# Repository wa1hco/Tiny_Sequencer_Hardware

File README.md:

# Tiny_Sequencer_Hardware
Schematic, Layout, and component files  
KiCad V8 used for schematic and layout  
ATTiny814 microcontroller  
FTDI230 Serial interface  
Surface mount components  
Back side is grouind plane, a few jumpers, and no components  
Connections via 12 pin screw terminal header with 0.1 inch spacing  
- 4 contact closure outputs using AC/DC optoisolators  
- Key input with return
- 6 to 30V DC input and return

Powered by DC or USB  
Programming via UPDI over USB  
Software able to use serial port for communication  
Status LEDs
- 4 sequencer ouptuts,
- 5V,
- Tx serial activity
- Rx serial activity

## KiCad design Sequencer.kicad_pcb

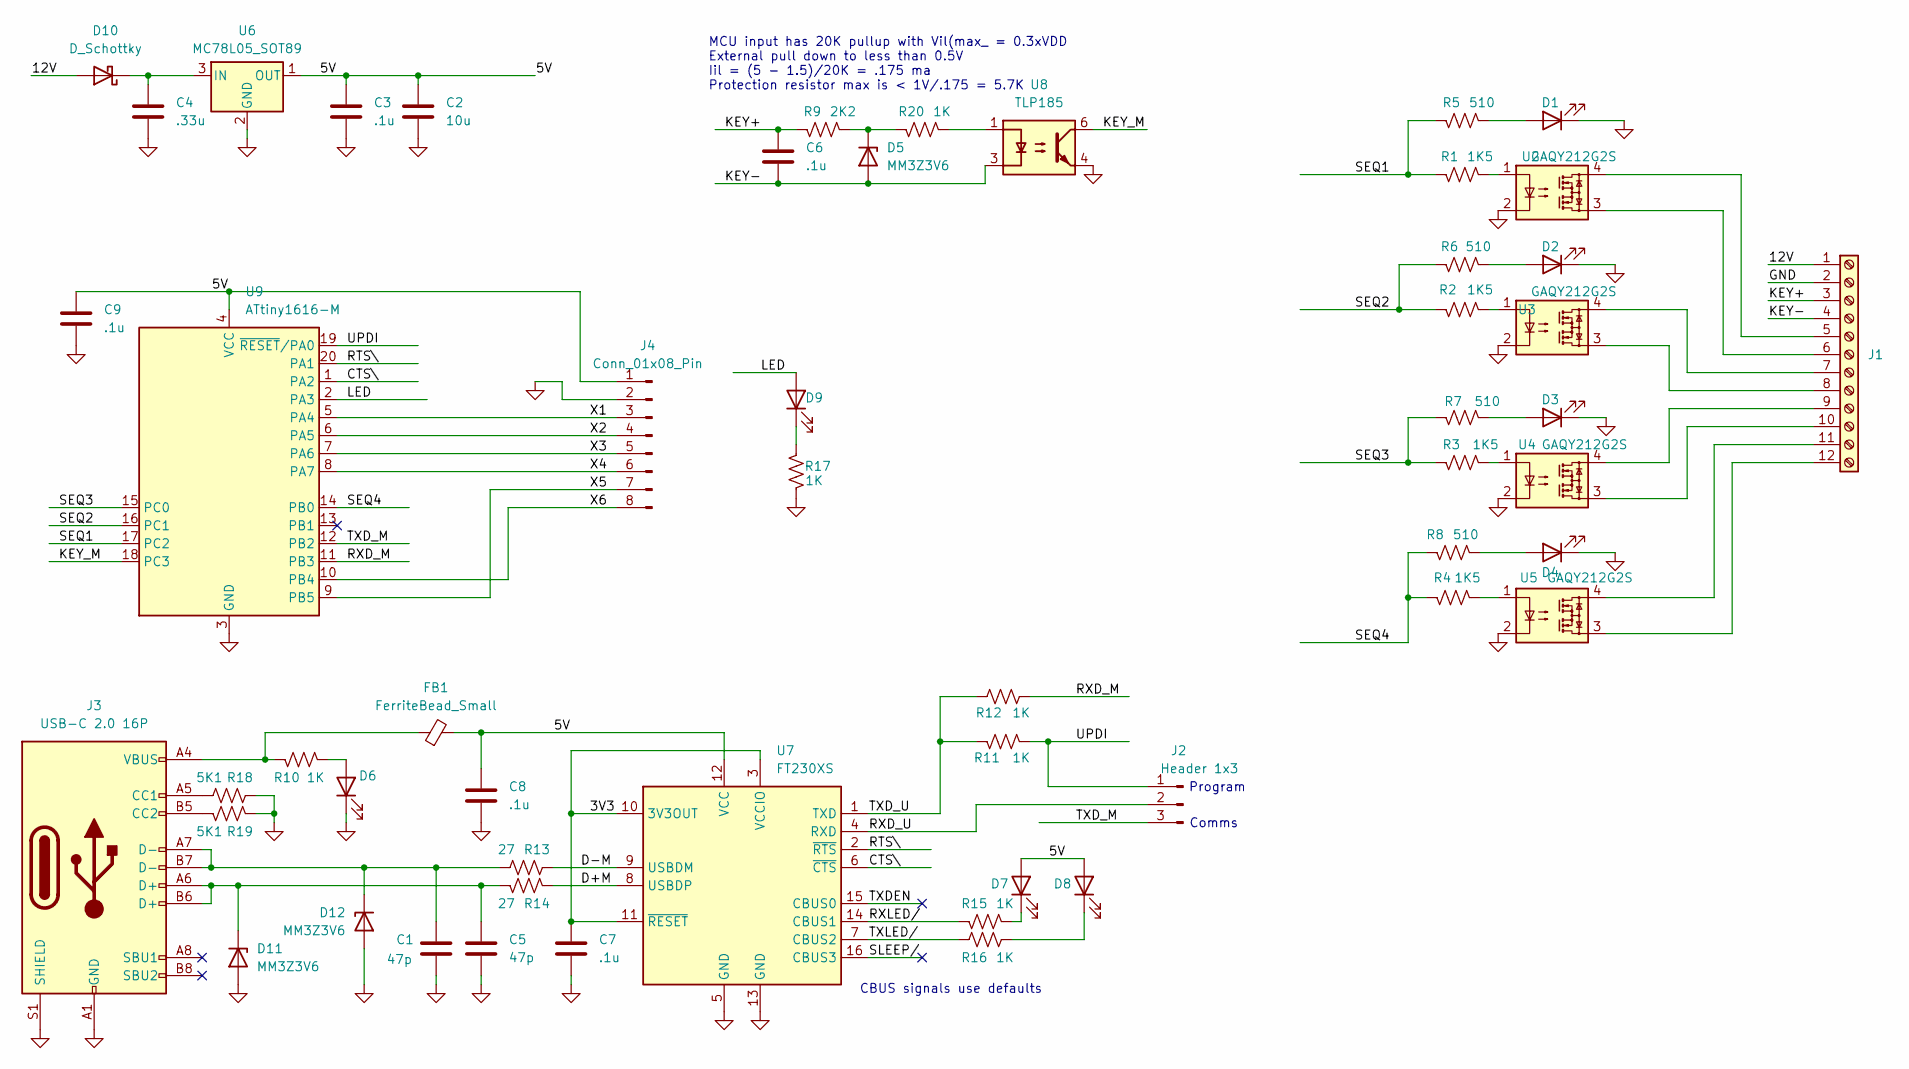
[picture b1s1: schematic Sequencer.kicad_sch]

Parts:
C1, C5: 47p; C_0603_1608Metric; LCSC PN C1671
C2: 10u; C_0603_1608Metric; LCSC PN C19702
C3, C6, C7, C8, C9: .1u; C_0603_1608Metric; LCSC PN C15849
C4: .33u; C_0603_1608Metric; LCSC PN C2918485
D1, D2, D3, D4: Red; LED_0603_1608Metric; LCSC PN C2286
D5, D11, D12: MM3Z3V6; D_SOD-323; LCSC PN C19077454
D6, D9: Green; LED_0603_1608Metric; LCSC PN C22371299
D7, D8: Yellow; LED_0603_1608Metric; LCSC PN C72038
D10: D_Schottky; D_0603_1608Metric; LCSC PN C143772
FB1: FerriteBead_Small; L_0805_2012Metric; LCSC PN C1017
J1: Screw_Terminal_01x12; TerminalBlock_TE_1-282834-2_1x12_P2.54mm_Horizontal; LCSC PN C474929
J2: Header 1x3; PinHeader_1x03_P2.54mm_Vertical; LCSC PN C6332196
J3: USB-C 2.0 16P; USB_C_Receptacle_G-Switch_GT-USB-7010ASV; LCSC PN C2835315
J4: Conn_01x08_Pin; PinHeader_1x08_P2.54mm_Vertical; LCSC PN C18078205
R1, R2, R3, R4: 1K5; R_0603_1608Metric; LCSC PN C22843
R5, R6, R7, R8: 510; R_0603_1608Metric; LCSC PN C23193
R9: 2K2; R_0603_1608Metric; LCSC PN C4190
R10, R11, R12, R15, R16, R17, R20: 1K; R_0603_1608Metric; LCSC PN C21190
R13, R14: 27; R_0603_1608Metric; LCSC PN C25190
R18, R19: 5K1; R_0603_1608Metric; LCSC PN C23186
U2, U3, U4, U5: GAQY212G2S; SO-4_4.4x3.9mm_P2.54mm; LCSC PN C7435109
U6: MC78L05_SOT89; SOT-89-3; LCSC PN C5346137
U7: FT230XS; SSOP-16_3.9x4.9mm_P0.635mm; LCSC PN C69082
U8: TLP185; SOIC-4_4.55x3.7mm_P2.54mm; LCSC PN C17695768
U9: ATtiny1616-M; VQFN-20-1EP_3x3mm_P0.4mm_EP1.7x1.7mm

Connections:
/3V3: C7.1, U7.3 (VCCIO), U7.10 (3V3OUT), U7.11 (~RESET)
/5V: C2.1, C3.1, C8.1, C9.1, D7.2 (A), D8.2 (A), FB1.2, J4.1, U6.1 (OUT), U7.12 (VCC), U9.4 (VCC)
/12V: D10.2 (A), J1.1
/CTS\: U7.6 (~CTS), U9.1 (PA2)
/D+M: R14.1, U7.8 (USBDP)
/D-M: R13.1, U7.9 (USBDM)
/KEY+: C6.1, J1.3, R9.1
/KEY-: C6.2, D5.2 (A), J1.4, U8.3
/KEY_M: U8.6, U9.18 (PC3)
/LED: D9.2 (A), U9.2 (PA3)
/RTS\: U7.2 (~RTS), U9.20 (PA1)
/RXD_M: R12.2, U9.11 (PB3)
/RXD_U: J2.2, U7.4 (RXD)
/RXLED/: R15.1, U7.14 (CBUS1)
/SEQ1: R1.1, R5.1, U9.17 (PC2)
/SEQ2: R2.1, R6.1, U9.16 (PC1)
/SEQ3: R3.1, R7.1, U9.15 (PC0)
/SEQ4: R4.1, R8.1, U9.14 (PB0)
/SLEEP/: U7.16 (CBUS3)
/TXDEN: U7.15 (CBUS0)
/TXD_M: J2.3, U9.12 (PB2)
/TXD_U: R11.1, R12.1, U7.1 (TXD)
/TXLED/: R16.1, U7.7 (CBUS2)
/UPDI: J2.1, R11.2, U9.19 (~RESET/PA0)
/X1: J4.3, U9.5 (PA4)
/X2: J4.4, U9.6 (PA5)
/X3: J4.5, U9.7 (PA6)
/X4: J4.6, U9.8 (PA7)
/X5: J4.7, U9.9 (PB5)
/X6: J4.8, U9.10 (PB4)
GND: C1.2, C2.2, C3.2, C4.2, C5.2, C7.2, C8.2, C9.2, D1.1 (K), D2.1 (K), D3.1 (K), D4.1 (K), D6.1 (K), D11.2 (A), D12.2 (A), J1.2, J3.A1 (GND), J3.A12 (GND), J3.B1 (GND), J3.B12 (GND), J3.S1 (SHIELD), J4.2, R17.2, R18.1, R19.1, U2.2, U3.2, U4.2, U5.2, U6.2 (GND), U7.5 (GND), U7.13 (GND), U8.4, U9.3 (GND), U9.21 (GND)
unnamed: D1.2 (A), R5.2
unnamed: D2.2 (A), R6.2
unnamed: D3.2 (A), R7.2
unnamed: D4.2 (A), R8.2
unnamed: D5.1 (K), R9.2, R20.1
unnamed: D6.2 (A), R10.1
unnamed: D7.1 (K), R15.2
unnamed: D8.1 (K), R16.2
unnamed: D9.1 (K), R17.1
unnamed: C4.1, D10.1 (K), U6.3 (IN)
unnamed: C5.1, D11.1 (K), J3.A6 (D+), J3.B6 (D+), R14.2
unnamed: C1.1, D12.1 (K), J3.A7 (D-), J3.B7 (D-), R13.2
unnamed: FB1.1, J3.A4 (VBUS), J3.A9 (VBUS), J3.B4 (VBUS), J3.B9 (VBUS), R10.2
unnamed: J1.5, U2.4
unnamed: J1.6, U2.3
unnamed: J1.7, U3.4
unnamed: J1.8, U3.3
unnamed: J1.9, U4.4
unnamed: J1.10, U4.3
unnamed: J1.11, U5.4
unnamed: J1.12, U5.3
unnamed: J3.A5 (CC1), R18.2
unnamed: J3.B5 (CC2), R19.2
unnamed: R1.2, U2.1
unnamed: R2.2, U3.1
unnamed: R3.2, U4.1
unnamed: R4.2, U5.1
unnamed: R20.2, U8.1

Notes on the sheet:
CBUS signals use defaults
MCU input has 20K pullup with Vil(max_ = 0.3xVDD External pull down to less than 0.5V Iil = (5 - 1.5)/20K = .175 ma Protection resistor max is < 1V/.175 = 5.7K
Program
Comms

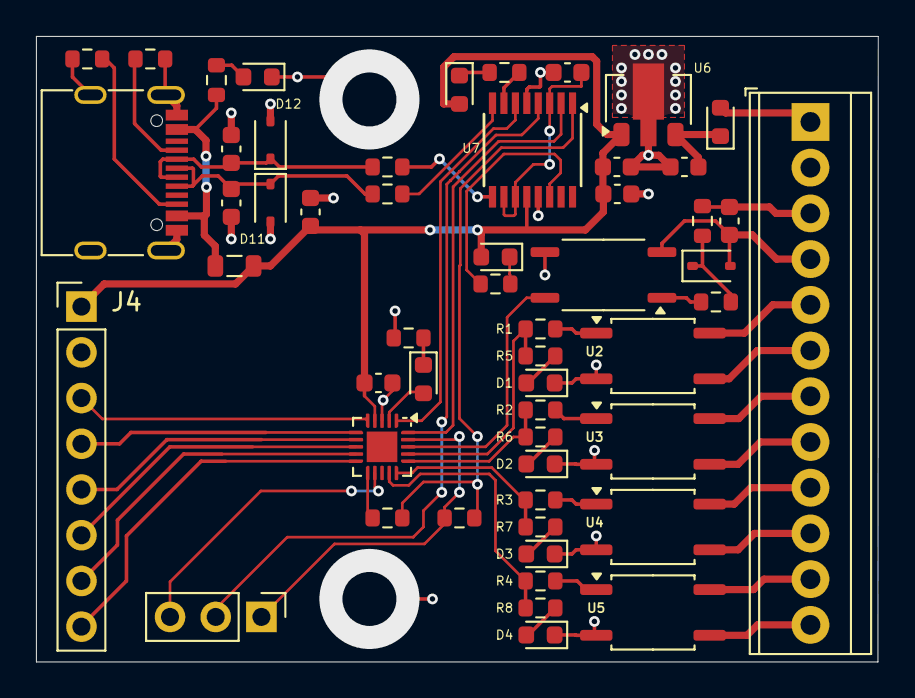
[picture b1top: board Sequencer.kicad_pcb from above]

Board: 2 copper layers, 46.8 x 34.8 mm, 54 parts (0 on the bottom side), 57 nets.

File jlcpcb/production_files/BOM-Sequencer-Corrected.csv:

Comment,Designator,Footprint,LCSC,Quantity,Description
47p,"C1,C5",C_0603_1608Metric,C1671,2,50V 47pF C0G ±5% 0603 Multilayer Ceramic Capacitors
6.8u,C2,C_0603_1608Metric,C338096,1,10V 6.8uF  X5R ±10% 0603 Multilayer Ceramic Capacitors
.1u,"C3,C4,C6,C7,C8,C9",C_0603_1608Metric,C14663,5,50V 100nF X7R ±10% 0603 Multilayer Ceramic Capacitors
0.33u,C4,C_0603_1608Metric,C292682,,50V 330nF X7R ±10% 0603 Multilayer Ceramic Capacitors 
Red,"D1,D2,D3,D4",LED_0603_1608Metric,C2286,4,-40℃~+85℃ Red 0603 LED Indication
D_Schottky,D10,D_0603_1608Metric,C143772,1,40V 450mV@200mA 200mA 0603 Schottky Diodes
MM3Z3V6,"D11,D12,D5",D_SOD-323,C891617,3,Independent Type 3.42V~3.78V 200mW 3.6V SOD-323FL Zener Diodes
Green,"D6,D7,D8,D9",LED_0603_1608Metric,C965806,4,20mA 240mcd 565nm~575nm -20℃~+85℃ Positive Stick Yellow Green 120° 50mW 2.4V 0603 LED
FerriteBead_Small,FB1,L_0805_2012Metric,C1017,1,300mΩ ±25% 600Ω@100MHz 0805 Ferrite Beads
Screw_Terminal_01x12,J1,TerminalBlock_TE_1-282834-2_1x12_P2.54mm_Horizontal,C5188451,1,Copper Alloy 1x12P Tin 2.54mm 1 1 12 6A -40℃~+105℃ 150V Green 18~24
Header 1x3,J2,PinHeader_1x03_P2.54mm_Vertical,C6332196,1,Gold 250V 3A 2.54mm 3P 6mm -40℃~+105℃ 3mm 2.54mm Brass Black Single
USB-C 2.0 16P,J3,USB_C_Receptacle_G-Switch_GT-USB-7010ASV,C2988369,1,USB 2.0 3A 1 Horizontal attachment 16P Female -40℃~+85℃ Gold Type-C
Conn_01x08_Pin,J4,PinHeader_1x08_P2.54mm_Vertical,C18078205,1,Gold 1kV 3A 2.5mm 8P 6mm -40℃~+105℃ 3mm 2.54mm Brass Black Single Row 1x8PPin Headers
1K5,"R1,R2,R3,R4",R_0603_1608Metric,C22843,4,100mW Thick Film Resistors 75V ±100ppm/℃ ±1% 1.5kΩ 0603 Chip Resistor
1K5,"R5,R6,R7,R8",R_0603_1608Metric,C23193,4,100mW Thick Film Resistors 75V ±100ppm/℃ ±1% 510Ω 0603 Chip Resistor
1K,"R10,R11,R12,R15,R16,R17,R20",R_0603_1608Metric,C21190,7,100mW Thick Film Resistors 75V ±100ppm/℃ ±1% 1kΩ 0603 Chip Resistor
27R,"R13,R14,R18,R19",R_0603_1608Metric,C25190,2,100mW Thick Film Resistors 75V ±1% ±200ppm/℃ 27Ω 0603 Chip Resistor
5K1,"R18, R19",R_0603_1608Metric,C23186,2,100mW Thick Film Resistors 75V ±100ppm/℃ ±1% 5.1kΩ 0603 Chip Resistor
2K2,R9,R_0603_1608Metric,C4190,1,100mW Thick Film Resistors 75V ±100ppm/℃ ±1% 2.2kΩ 0603 Chip Resistor
GAQY212G2S,"U2,U3,U4,U5",SO-4_4.4x3.9mm_P2.54mm,C7435109,4,1 Form A(SPST-NO) 1.2V 60V 68mΩ 1.8A SOP-4 Solid State Relays (MOS Output)
MC78L05_SOT89,U6,SOT-89-3,C71136,1,100mA Fixed 5V Positive electrode 30V SOT-89-3 Voltage Regulators
FT230XS,U7,SSOP-16_3.9x4.9mm_P0.635mm,C69082,1,USB to UART UART SSOP-16-150mil USB Converters
TLP185,U8,SOIC-4_4.55x3.7mm_P2.54mm,C17695768,1,"3.75kV 50mA 1 1.25V SOIC-4-175mil Transistor, Photovoltaic Output Optoisolators"
ATtiny1616-M,U9,VQFN-20-1EP_3x3mm_P0.4mm_EP1.7x1.7mm,C507118,1,16KB 1.8V~5.5V AVR 2KB 20MHz FLASH 18 QFN-20-EP(3x3) Microcontrollers

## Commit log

2024-09-19 Sequencer schematic and partial pcb layout
2024-09-19 Completed layout, passed DRC Images of front and back
2024-09-19 .gitignore .lck files
2024-09-19 Added MCU controlled LED Changed bottom fill to cover two resistors
2024-09-21 Converted to USB-C connector Added zener protection to USB data wires Shuffled layout to reduce jumpers Generated BOM and gerbers for experimenting with JLCPCB
2024-09-23 middle of trying to remove some jumpers and make wiring more direct Trying to create room for reverse polarity protection on 12V
2024-10-10 Added optocoupler on KEY line Changed to ATTinyx16 processor with 20 pins Serial select for UPDI vs Serial comms is now a pin header Added pin header for other unused signals on MCU
2024-10-17 small schematic rearrangement
2024-10-20 Finalized design for release to JCLPCB Add terminal block library Added some data sheets for terminal block, USB-C connector, etc
2024-10-20 Added another datasheet
2024-10-21 Added USB-C connector footprints Changed ATTiny from SOIC-20 to 3x3 mm QFP
2024-10-21 removed previous gerber and other prodution files added jlcpcb related production files update license to cc BY-SA 4.0
2024-12-06 This records the status of the board after fixing component values from first build. Sent this to JLCPCB, but they found and error in FT230 package selection. Parts availability says it needs to chan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
2024-12-06 Changed usb serial to FT231 because it's in stock. Layout cleanups.
2024-12-07 These files were used for the JLCPCB Y7 build, Dec 6, 2024
